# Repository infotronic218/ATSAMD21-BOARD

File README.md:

# ATSAMD21-BOARD  designed Within Kicad 6
The aim of this project is to design a simple development board for ARM Based MCU line of Microchip for quick use and experimentation of the MCU interfaces. Severals sensors and modules are connected to the MCU interfaces for quick code implementation and testing.
## Used main components in the design 
+ Microchip MCU  ATSAMD21G17D-A
+ UART/USB Transceiver for debugging
+ SW Debug interface over JLINK
+ Bluetooth module (DA14531MOD) over UART 
+ LORA Module (RFM95W) over SPI
+ LED Driver (IS31FL3737) over I2C
+ Lion Battery charger (MCP73831-2-OT)
+ FLASH Memory (16Mbits) Over SPI
+ Temperature and humidity sensor (SHT40) over I2C
+ Digital LED (IN-PI554FCH)
+ GPIO exposed pins 
## PCB LAYOUT VIEWS 
 
1. TOP LAYER LAYOUT 

2. BOTTOM LAYER LAYOUT

3. 3D VIEW

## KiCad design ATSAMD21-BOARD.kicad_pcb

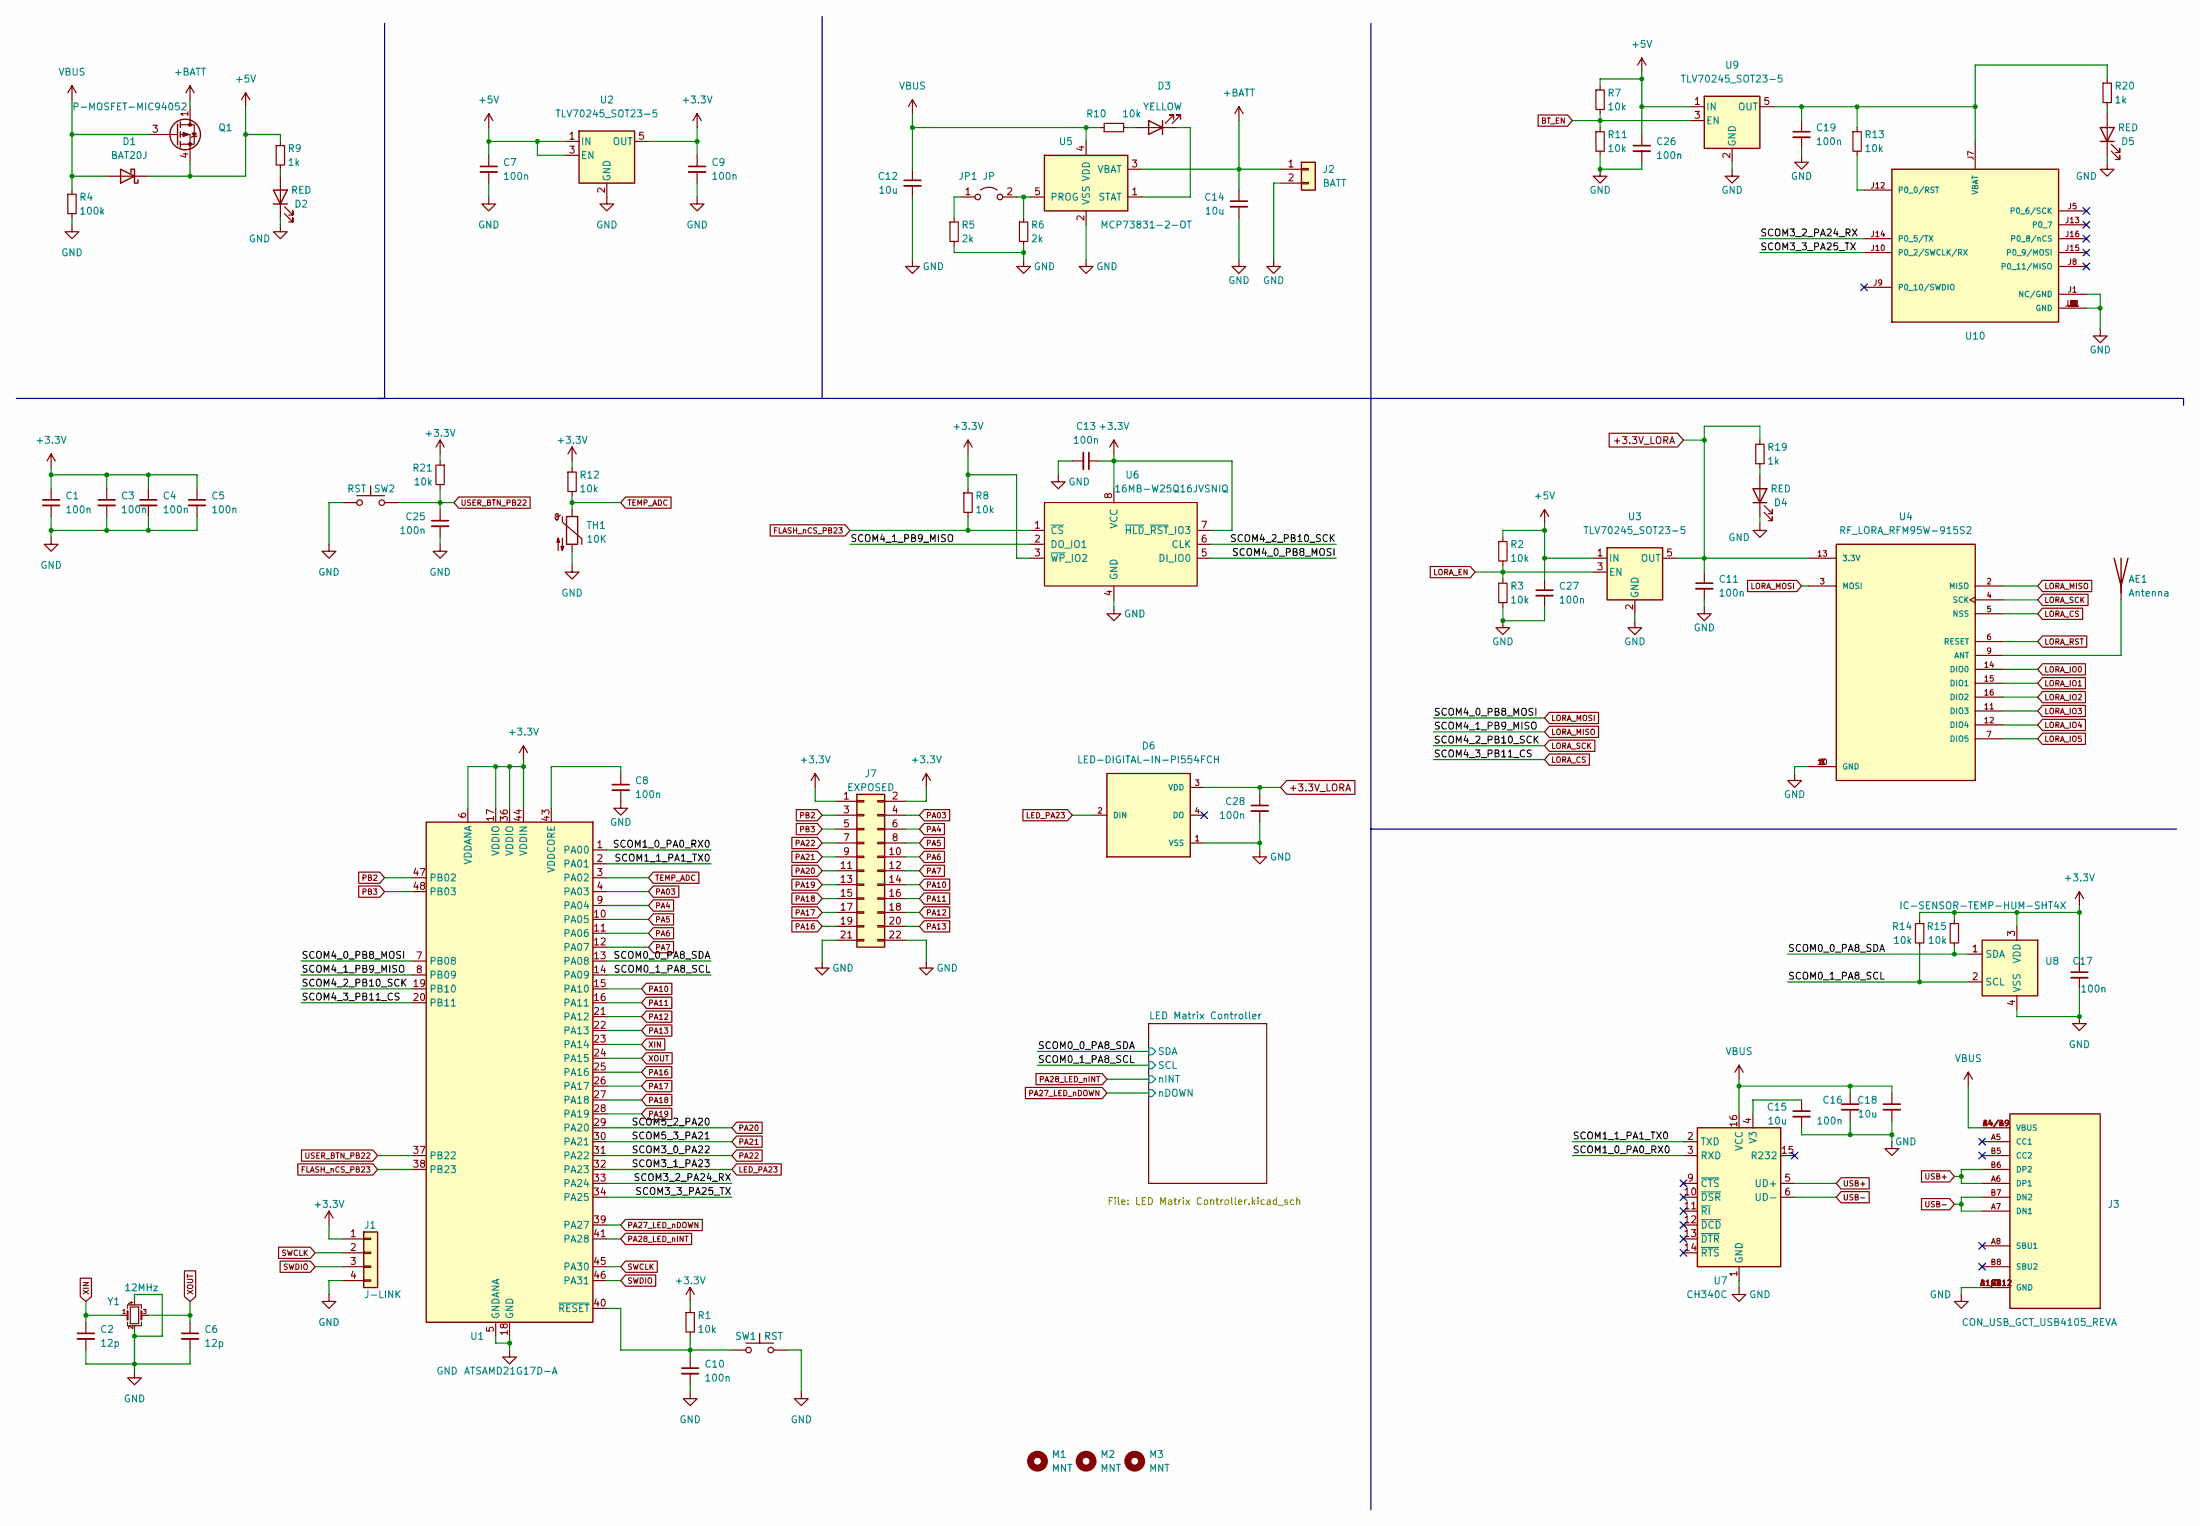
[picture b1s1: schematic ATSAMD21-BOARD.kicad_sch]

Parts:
AE1: Antenna; CON_ANTENNA_1PIN
C1, C3, C4, C5, C7, C8, C9, C10, C11, C13, C16, C17, C19, C25, C26, C27, C28: 100n; C_0603_1608Metric
C2, C6: 12p; C_0603_1608Metric
C12, C14, C15, C18: 10u; C_0805_2012Metric
D1: BAT20J; D_SOD-123F
D2: RED; LED_0805_2012Metric
D3: YELLOW; LED_0805_2012Metric
D4, D5: RED; LED_0603_1608Metric
D6: LED-DIGITAL-IN-PI554FCH
J1: J-LINK; PinHeader_1x04_P2.54mm_Vertical
J2: BATT; JST_XH_B2B-XH-A_1x02_P2.50mm_Vertical
J3: CON_USB_GCT_USB4105_REVA; PARTREV 0.2
J7: EXPOSED; PinHeader_2x11_P2.54mm_Vertical
JP1: JP; SolderJumper-2_P1.3mm_Open_RoundedPad1.0x1.5mm
M1, M2, M3: MNT; MountingHole_2.1mm
Q1: P-MOSFET-MIC94052; SOT-363_SC-70-6
R1, R2, R3, R7, R11, R14, R15, R21: 10k; R_0603_1608Metric
R4: 100k; R_0805_2012Metric
R5, R6: 2k; R_0603_1608Metric
R8, R10, R12, R13: 10k; R_0805_2012Metric
R9: 1k; R_0805_2012Metric
R19, R20: 1k; R_0603_1608Metric
SW1, SW2: RST; SW_Push_1P1T_NO_CK_KMR2
TH1: 10K; R_0805_2012Metric
U1: ATSAMD21G17D-A; TQFP-48_7x7mm_P0.5mm
U2, U3, U9: TLV70245_SOT23-5; SOT-23-5
U4: RF_LORA_RFM95W-915S2
U5: MCP73831-2-OT; SOT-23-5
U6: 16MB-W25Q16JVSNIQ; IC-FLASH-16MB-W25Q16JVSNIQ; MPN W25Q16JVSNIQ; Mouser 454-W25Q16JVSNIQ
U7: CH340C; SOIC-16_3.9x9.9mm_P1.27mm
U8: IC-SENSOR-TEMP-HUM-SHT4X; MPN SHT40-AD1B-R3; Mouser 403-SHT40-AD1B-R3
U10: DA14531MOD-00F01002
Y1: 12MHz; Crystal_SMD_3225-4Pin_3.2x2.5mm

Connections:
+3.3V: C1.1, C3.1, C4.1, C5.1, C9.1, C13.1, C17.1, J1.1, J7.1, J7.2, R1.1, R8.1, R12.1, R14.1, R15.1, R21.1, U1.6 (VDDANA), U1.17 (VDDIO), U1.36 (VDDIO), U1.44 (VDDIN), U2.5 (OUT), U6.3 (~WP_IO2), U6.7 (~HLD_~RST_IO3), U6.8 (VCC), U8.3 (VDD); also elsewhere on the board
+3.3V_LORA: C11.1, C28.1, D6.3 (VDD), R19.1, U3.5 (OUT), U4.13 (3.3V)
+5V: C7.1, C26.1, C27.1, D1.1 (K), Q1.4 (S), R2.1, R7.1, R9.1, U2.1 (IN), U2.3 (EN), U3.1 (IN), U9.1 (IN); also elsewhere on the board
+BATT: C14.1, J2.1, Q1.1 (D), Q1.2 (S), Q1.5 (D), Q1.6 (D), U5.3 (VBAT)
/SCOM0_0_PA8_SDA: R15.2, U1.13 (PA08), U8.1 (SDA); also elsewhere on the board
/SCOM0_1_PA8_SCL: R14.2, U1.14 (PA09), U8.2 (SCL); also elsewhere on the board
/SCOM1_0_PA0_RX0: U1.1 (PA00), U7.3 (RXD)
/SCOM1_1_PA1_TX0: U1.2 (PA01), U7.2 (TXD)
/SCOM3_2_PA24_RX: U1.33 (PA24), U10.J14 (P0_5/TX)
/SCOM3_3_PA25_TX: U1.34 (PA25), U10.J10 (P0_2/SWCLK/RX)
BT_EN: R7.2, R11.1, U9.3 (EN)
FLASH_nCS_PB23: R8.2, U1.38 (PB23), U6.1 (~CS)
GND: C1.2, C2.2, C3.2, C4.2, C5.2, C6.2, C7.2, C8.2, C9.2, C10.2, C11.2, C12.2, C13.2, C14.2, C15.2, C16.2, C17.2, C18.2, C19.2, C25.2, C26.2, C27.2, C28.2, D2.1 (K), D4.1 (K), D5.1 (K), D6.1 (VSS), J1.4, J2.2, J3.A1/B12 (GND), J3.B1/A12 (GND), J3.G1 (GND), J3.G2 (GND), J3.G3 (GND), J3.G4 (GND), J7.21, J7.22, R3.2, R4.2, R5.2, R6.2, R11.2, SW1.2, SW2.2, TH1.2, U1.5 (GNDANA), U1.18 (GND), U1.35 (GND), U1.42 (GND), U2.2 (GND), U3.2 (GND), U4.1 (GND), U4.8 (GND), U4.10 (GND), U5.2 (VSS), U6.4 (GND), U7.1 (GND), U8.4 (VSS), U9.2 (GND), U10.J1 (NC/GND), U10.J2 (GND), U10.J3 (GND), U10.J4 (GND), U10.J6 (GND), U10.J11 (GND), Y1.2, Y1.4; also elsewhere on the board
LED_PA23: D6.2 (DIN), U1.32 (PA23)
LORA_CS: U1.20 (PB11), U4.5 (NSS)
LORA_EN: R2.2, R3.1, U3.3 (EN)
LORA_IO0: U4.14 (DIO0)
LORA_IO1: U4.15 (DIO1)
LORA_IO2: U4.16 (DIO2)
LORA_IO3: U4.11 (DIO3)
LORA_IO4: U4.12 (DIO4)
LORA_IO5: U4.7 (DIO5)
LORA_MISO: U1.8 (PB09), U4.2 (MISO), U6.2 (DO_IO1)
LORA_MOSI: U1.7 (PB08), U4.3 (MOSI), U6.5 (DI_IO0)
LORA_RST: U4.6 (RESET)
LORA_SCK: U1.19 (PB10), U4.4 (SCK), U6.6 (CLK)
unnamed: AE1.1 (A), U4.9 (ANT)
unnamed: C8.1, U1.43 (VDDCORE)
unnamed: C10.1, R1.2, SW1.1, U1.40 (~RESET)
unnamed: C15.1, U7.4 (V3)
unnamed: C19.1, R13.1, R20.1, U9.5 (OUT), U10.J7 (VBAT)
unnamed: D2.2 (A), R9.2
unnamed: D3.1 (K), U5.1 (STAT)
unnamed: D3.2 (A), R10.2
unnamed: D4.2 (A), R19.2
unnamed: D5.2 (A), R20.2
unnamed: JP1.1 (A), R5.1
unnamed: JP1.2 (B), R6.1, U5.5 (PROG)
unnamed: R13.2, U10.J12 (P0_0/RST)
PA03: J7.4, U1.4 (PA03)
PA4: J7.6, U1.9 (PA04)
PA5: J7.8, U1.10 (PA05)
PA6: J7.10, U1.11 (PA06)
PA7: J7.12, U1.12 (PA07)
PA10: J7.14, U1.15 (PA10)
PA11: J7.16, U1.16 (PA11)
PA12: J7.18, U1.21 (PA12)
PA13: J7.20, U1.22 (PA13)
PA16: J7.19, U1.25 (PA16)
PA17: J7.17, U1.26 (PA17)
PA18: J7.15, U1.27 (PA18)
PA19: J7.13, U1.28 (PA19)
PA20: J7.11, U1.29 (PA20)
PA21: J7.9, U1.30 (PA21)
PA22: J7.7, U1.31 (PA22)
PA27_LED_nDOWN: U1.39 (PA27); also elsewhere on the board
PA28_LED_nINT: U1.41 (PA28); also elsewhere on the board
PB2: J7.3, U1.47 (PB02)
PB3: J7.5, U1.48 (PB03)
SWCLK: J1.2, U1.45 (PA30)
SWDIO: J1.3, U1.46 (PA31)
TEMP_ADC: R12.2, TH1.1, U1.3 (PA02)
USB+: J3.A6 (DP1), J3.B6 (DP2), U7.5 (UD+)
USB-: J3.A7 (DN1), J3.B7 (DN2), U7.6 (UD-)
USER_BTN_PB22: C25.1, R21.2, SW2.1, U1.37 (PB22)
VBUS: C12.1, C16.1, C18.1, D1.2 (A), J3.A4/B9 (VBUS), J3.B4/A9 (VBUS), Q1.3 (G), R4.1, R10.1, U5.4 (VDD), U7.16 (VCC)
XIN: C2.1, U1.23 (PA14), Y1.1
XOUT: C6.1, U1.24 (PA15), Y1.3

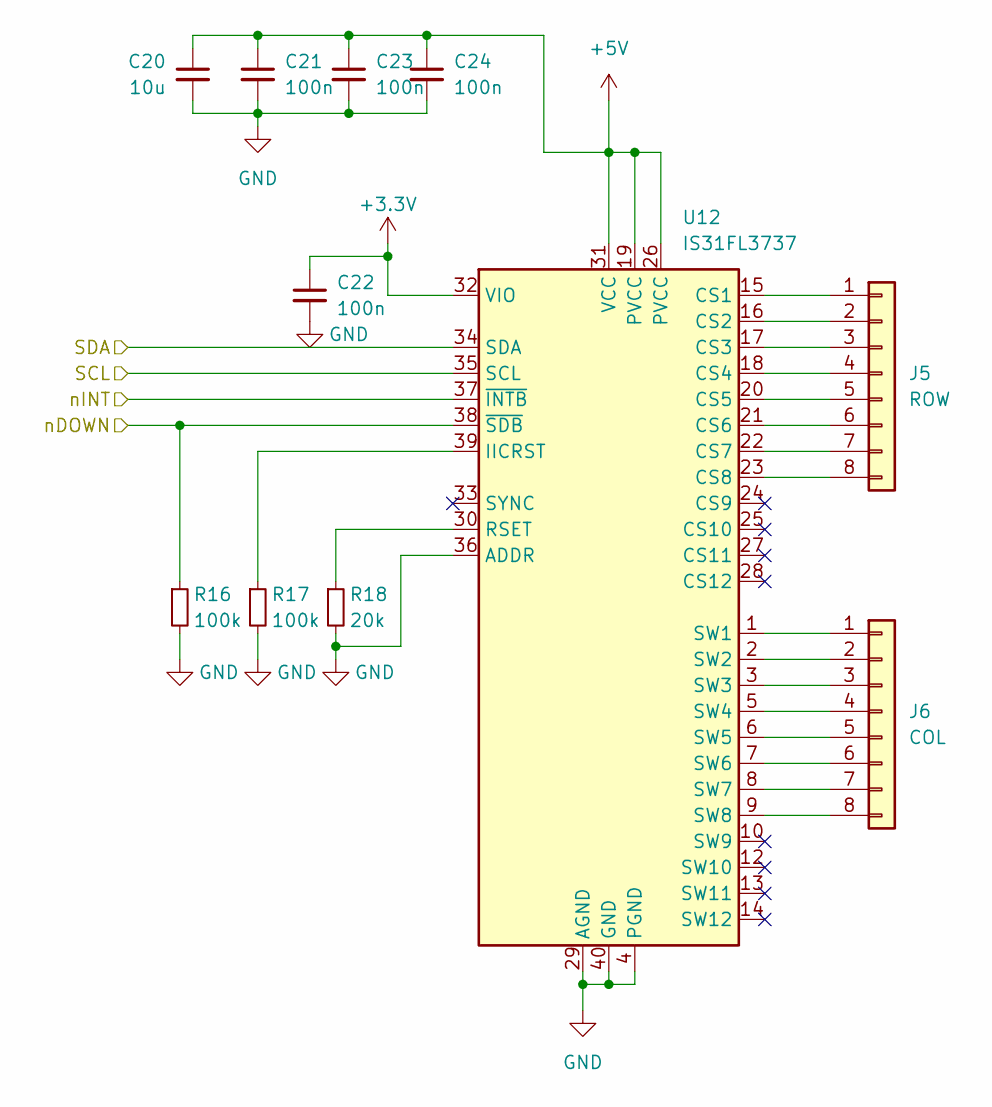
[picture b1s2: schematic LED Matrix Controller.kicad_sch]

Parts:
C20: 10u; C_0805_2012Metric
C21, C22, C23, C24: 100n; C_0603_1608Metric
J5: ROW; PinSocket_1x08_P2.54mm_Vertical
J6: COL; PinSocket_1x08_P2.54mm_Vertical
R16, R17: 100k; R_0603_1608Metric
R18: 20k; R_0603_1608Metric
U12: IS31FL3737; QFN-40-1EP_5x5mm_P0.4mm_EP3.6x3.6mm

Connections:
+3.3V: C22.1, U12.32 (VIO); also elsewhere on the board
+5V: C20.1, C21.1, C23.1, C24.1, U12.19 (PVCC), U12.26 (PVCC), U12.31 (VCC); also elsewhere on the board
/SCOM0_0_PA8_SDA: U12.34 (SDA); also elsewhere on the board
/SCOM0_1_PA8_SCL: U12.35 (SCL); also elsewhere on the board
GND: C20.2, C21.2, C22.2, C23.2, C24.2, R16.2, R17.2, R18.2, U12.4 (PGND), U12.11 (PGND), U12.29 (AGND), U12.36 (ADDR), U12.40 (GND), U12.41 (GND); also elsewhere on the board
unnamed: J5.1, U12.15 (CS1)
unnamed: J5.2, U12.16 (CS2)
unnamed: J5.3, U12.17 (CS3)
unnamed: J5.4, U12.18 (CS4)
unnamed: J5.5, U12.20 (CS5)
unnamed: J5.6, U12.21 (CS6)
unnamed: J5.7, U12.22 (CS7)
unnamed: J5.8, U12.23 (CS8)
unnamed: J6.1, U12.1 (SW1)
unnamed: J6.2, U12.2 (SW2)
unnamed: J6.3, U12.3 (SW3)
unnamed: J6.4, U12.5 (SW4)
unnamed: J6.5, U12.6 (SW5)
unnamed: J6.6, U12.7 (SW6)
unnamed: J6.7, U12.8 (SW7)
unnamed: J6.8, U12.9 (SW8)
unnamed: R17.1, U12.39 (IICRST)
unnamed: R18.1, U12.30 (RSET)
PA27_LED_nDOWN: R16.1, U12.38 (~SDB); also elsewhere on the board
PA28_LED_nINT: U12.37 (~INTB); also elsewhere on the board

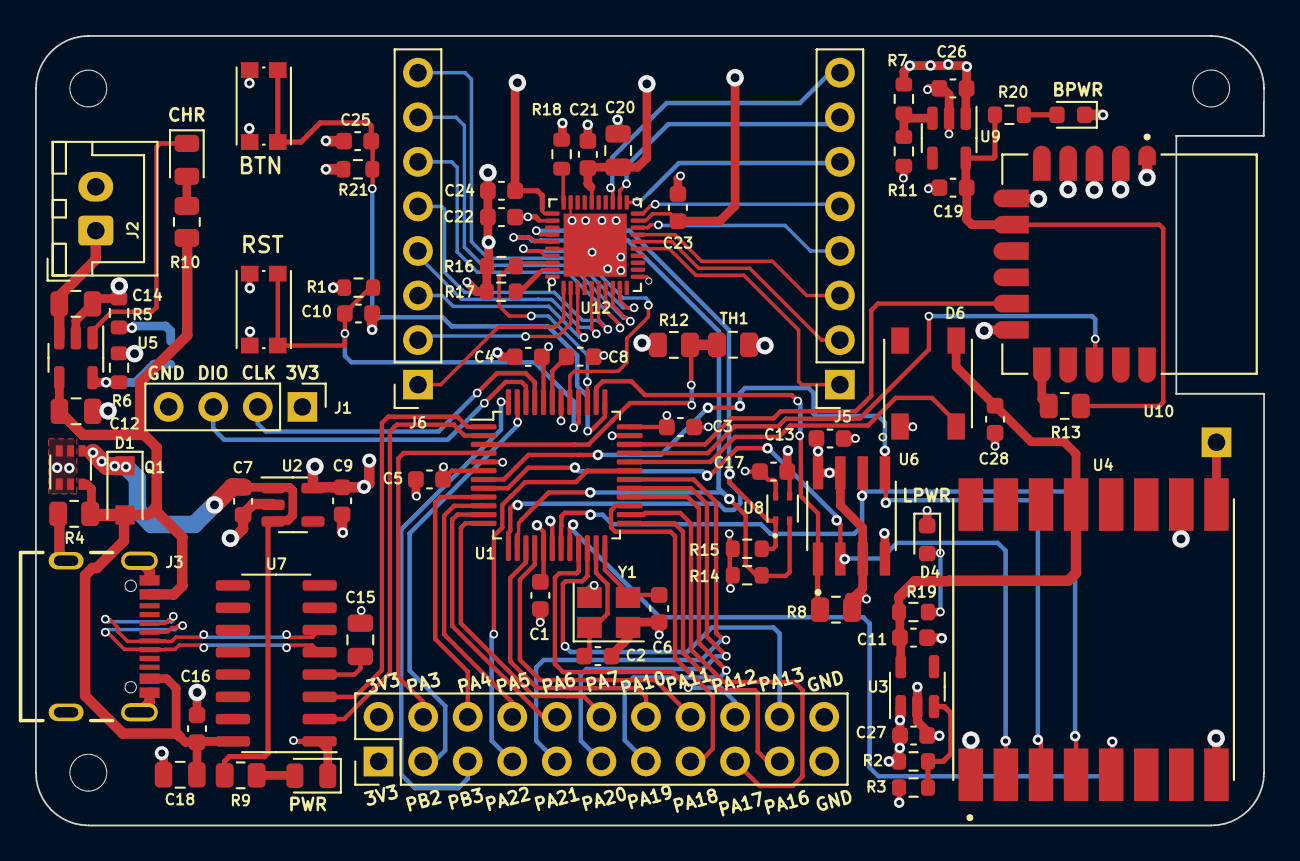
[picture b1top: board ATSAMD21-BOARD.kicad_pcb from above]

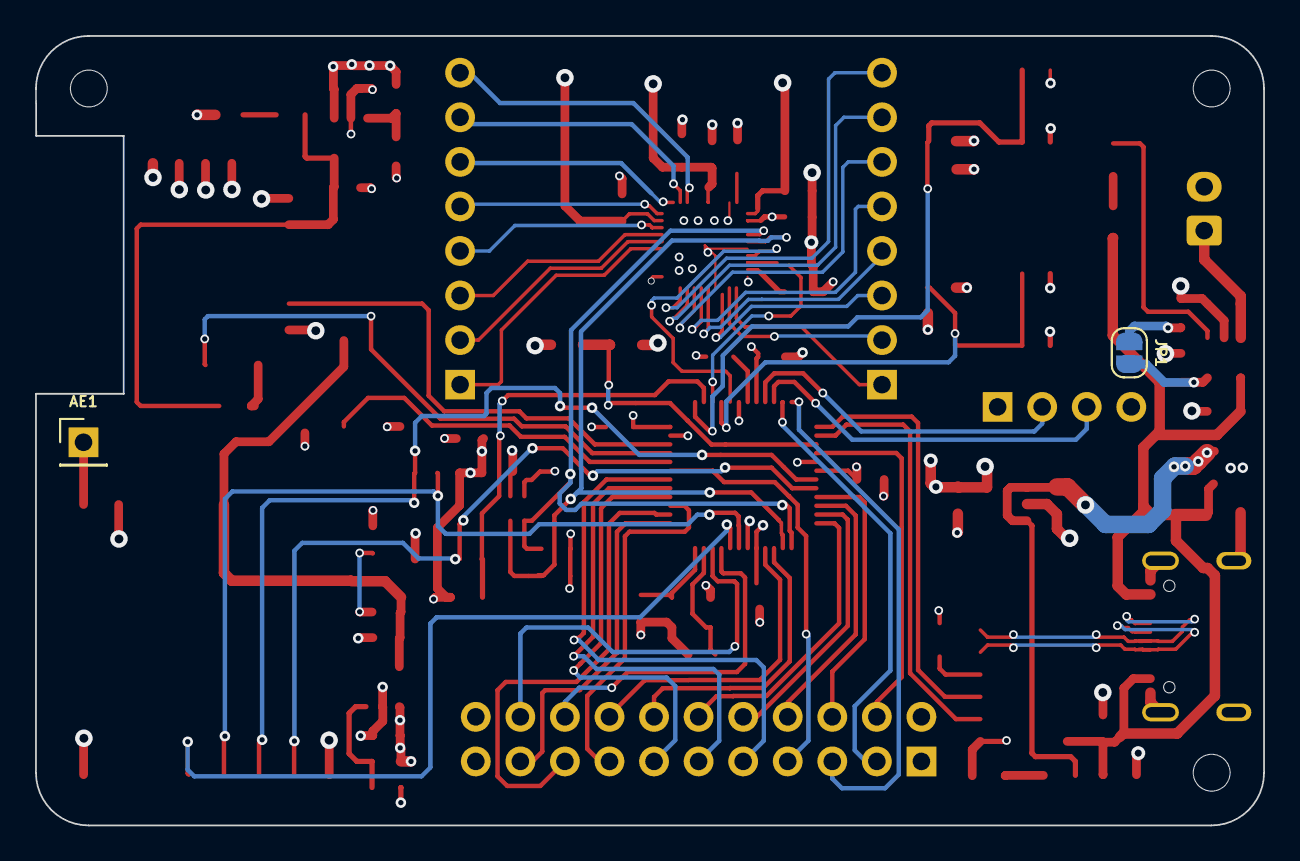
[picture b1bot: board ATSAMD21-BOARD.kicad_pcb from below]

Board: 4 copper layers, 70.0 x 45.0 mm, 82 parts (2 on the bottom side), 79 nets.

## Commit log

2022-10-23 First commit of the design
2022-10-23 Update the design
2022-10-23 Update the board design
2022-10-30 Update the board description
2022-10-30 Update the board
